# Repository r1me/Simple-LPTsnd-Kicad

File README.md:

# Simple-LPTsnd
Covox Speech Thing Clone / DAC for LPT Port

Added SMD 1206 revision made in Kicad 6

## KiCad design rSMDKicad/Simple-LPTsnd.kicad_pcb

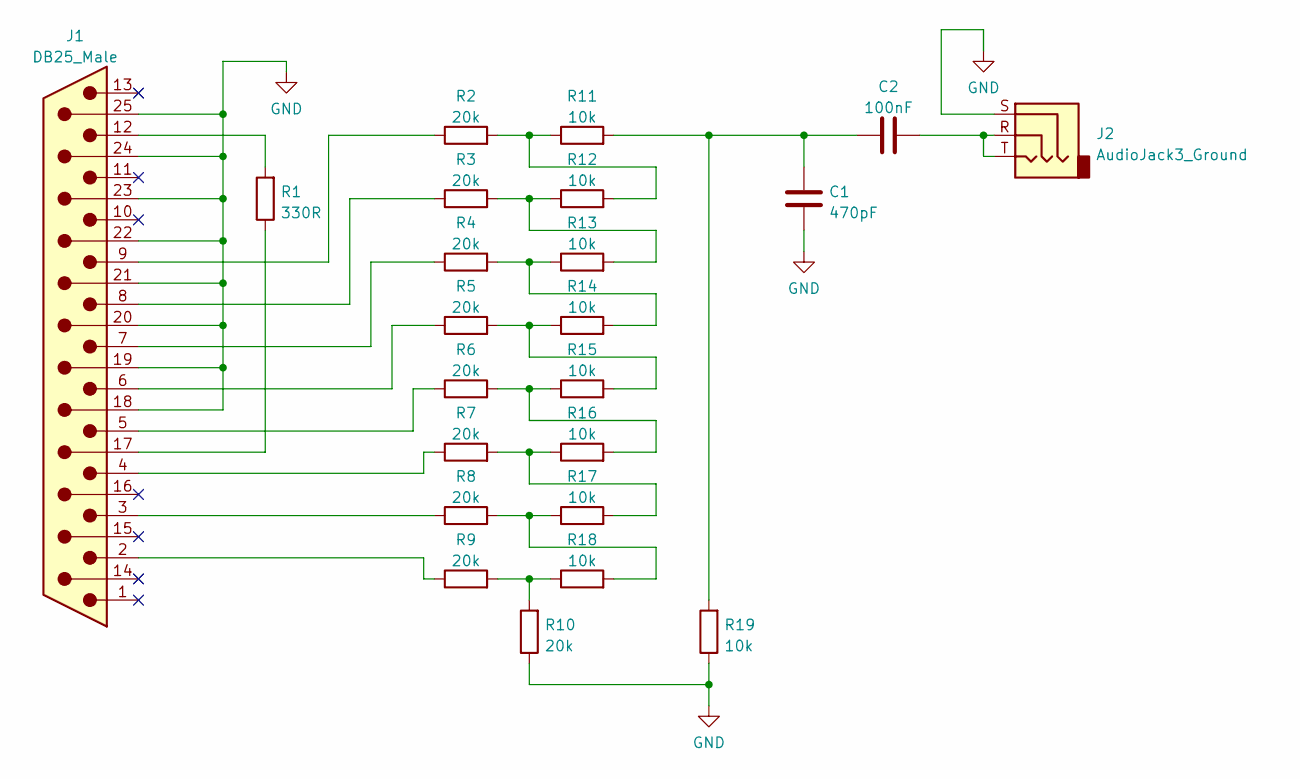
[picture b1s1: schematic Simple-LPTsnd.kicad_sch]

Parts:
C1: 470pF; C_1206_3216Metric_Pad1.33x1.80mm_HandSolder
C2: 100nF; C_1206_3216Metric_Pad1.33x1.80mm_HandSolder
J1: DB25_Male; DSUB-25_Male_Horizontal_P2.77x2.84mm_EdgePinOffset7.70mm_Ho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
J2: AudioJack3_Ground; CUI_SJ1-3525N
R1: 330R; R_1206_3216Metric_Pad1.30x1.75mm_HandSolder
R2, R3, R4, R5, R6, R7, R8, R9, R10: 20k; R_1206_3216Metric_Pad1.30x1.75mm_HandSolder
R11, R12, R13, R14, R15, R16, R17, R18, R19: 10k; R_1206_3216Metric_Pad1.30x1.75mm_HandSolder

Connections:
GND: C1.1, J1.18, J1.19, J1.20, J1.21, J1.22, J1.23, J1.24, J1.25, J2.S, R10.1, R19.1
unnamed: C1.2, C2.2, R11.2, R19.2
unnamed: C2.1, J2.R, J2.T
unnamed: J1.2, R9.1
unnamed: J1.3, R8.1
unnamed: J1.4, R7.1
unnamed: J1.5, R6.1
unnamed: J1.6, R5.1
unnamed: J1.7, R4.1
unnamed: J1.8, R3.1
unnamed: J1.9, R2.1
unnamed: J1.12, R1.2
unnamed: J1.17, R1.1
unnamed: R9.2, R10.2, R18.1
unnamed: R2.2, R11.1, R12.2
unnamed: R3.2, R12.1, R13.2
unnamed: R4.2, R13.1, R14.2
unnamed: R5.2, R14.1, R15.2
unnamed: R6.2, R15.1, R16.2
unnamed: R7.2, R16.1, R17.2
unnamed: R8.2, R17.1, R18.2

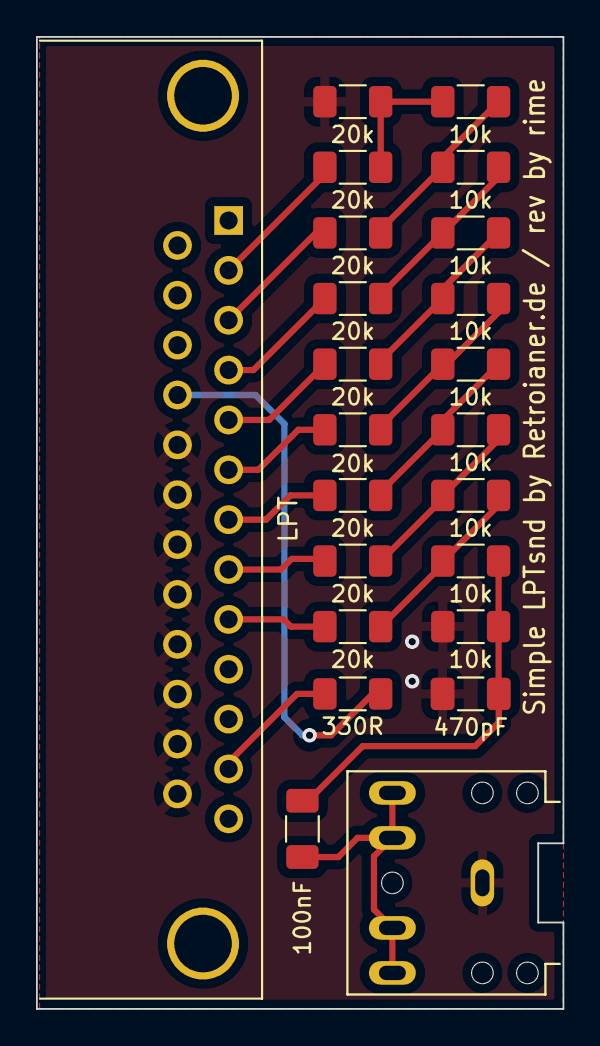
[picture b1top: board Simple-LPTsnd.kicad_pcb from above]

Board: 2 copper layers, 29.2 x 54.0 mm, 23 parts (0 on the bottom side), 21 nets.

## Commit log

2020-10-04 Create revision 0
2020-10-04 Add files via upload
    Eagle CAD Files for Simple LPTsnd r0
2020-10-04 Create revision 2
2021-02-21 Create LICENSE
2022-09-15 Added SMD 1206 revision made in Kicad 6
2022-09-15 Kicad render
